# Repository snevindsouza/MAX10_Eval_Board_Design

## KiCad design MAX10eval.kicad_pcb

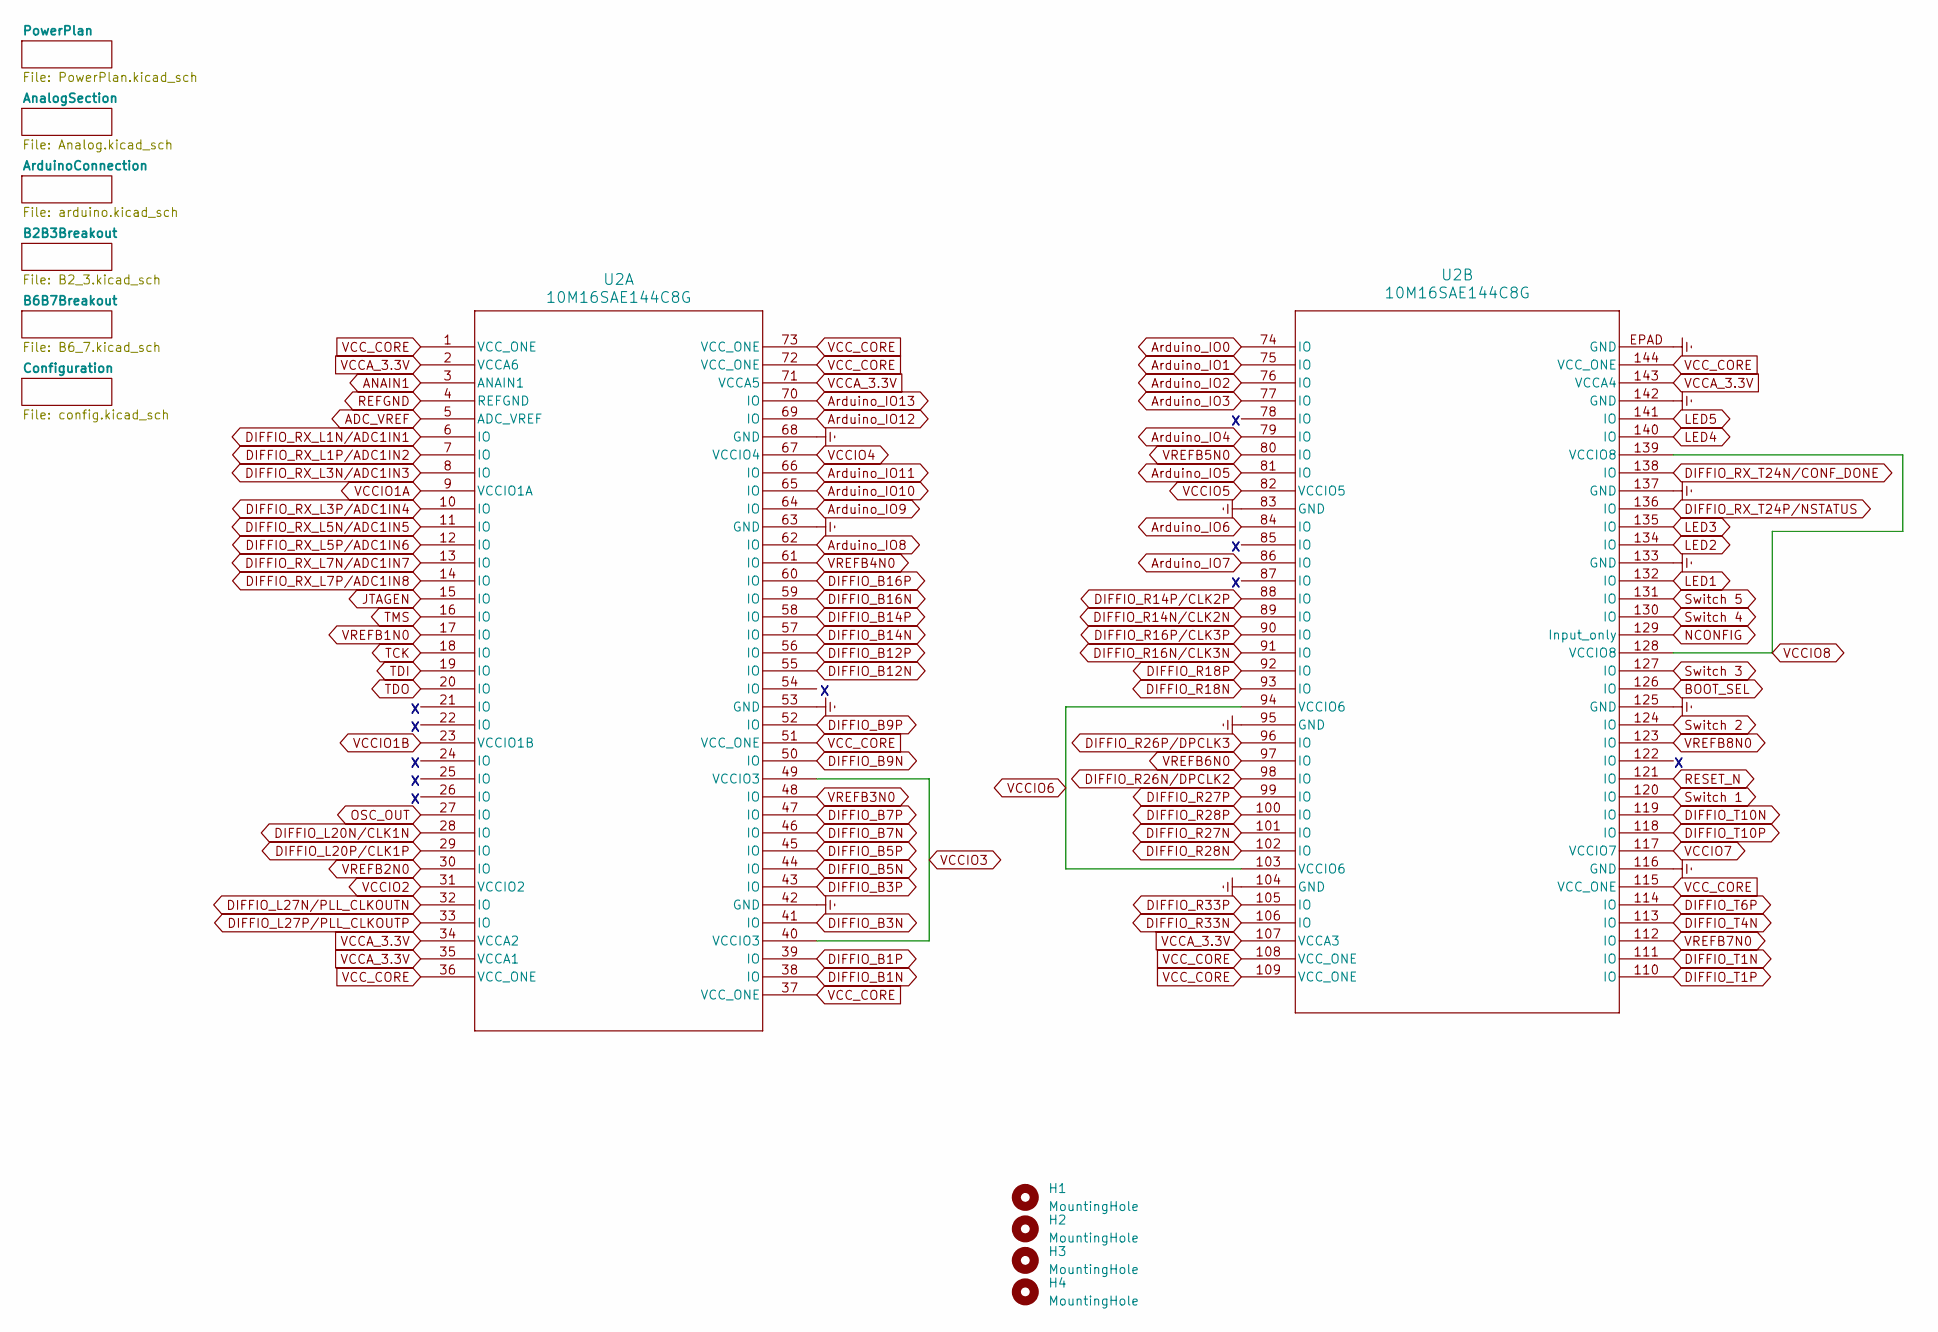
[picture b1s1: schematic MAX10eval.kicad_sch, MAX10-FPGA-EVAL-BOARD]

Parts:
H1, H2, H3, H4: MountingHole; MountingHole_3.2mm_M3
U2: 10M16SAE144C8G; 10M16SAE114C8G

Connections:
ADC_VREF: U2.5 (ADC_VREF); also elsewhere on the board
ANAIN1: U2.3 (ANAIN1); also elsewhere on the board
Arduino_IO0: U2.74 (IO); also elsewhere on the board
Arduino_IO1: U2.75 (IO); also elsewhere on the board
Arduino_IO2: U2.76 (IO); also elsewhere on the board
Arduino_IO3: U2.77 (IO); also elsewhere on the board
Arduino_IO4: U2.79 (IO); also elsewhere on the board
Arduino_IO5: U2.81 (IO); also elsewhere on the board
Arduino_IO6: U2.84 (IO); also elsewhere on the board
Arduino_IO7: U2.86 (IO); also elsewhere on the board
Arduino_IO8: U2.62 (IO); also elsewhere on the board
Arduino_IO9: U2.64 (IO); also elsewhere on the board
Arduino_IO10: U2.65 (IO); also elsewhere on the board
Arduino_IO11: U2.66 (IO); also elsewhere on the board
Arduino_IO12: U2.69 (IO); also elsewhere on the board
Arduino_IO13: U2.70 (IO); also elsewhere on the board
BOOT_SEL: U2.126 (IO); also elsewhere on the board
DIFFIO_B1N: U2.38 (IO); also elsewhere on the board
DIFFIO_B1P: U2.39 (IO); also elsewhere on the board
DIFFIO_B3N: U2.41 (IO); also elsewhere on the board
DIFFIO_B3P: U2.43 (IO); also elsewhere on the board
DIFFIO_B5N: U2.44 (IO); also elsewhere on the board
DIFFIO_B5P: U2.45 (IO); also elsewhere on the board
DIFFIO_B7N: U2.46 (IO); also elsewhere on the board
DIFFIO_B7P: U2.47 (IO); also elsewhere on the board
DIFFIO_B9N: U2.50 (IO); also elsewhere on the board
DIFFIO_B9P: U2.52 (IO); also elsewhere on the board
DIFFIO_B12N: U2.55 (IO); also elsewhere on the board
DIFFIO_B12P: U2.56 (IO); also elsewhere on the board
DIFFIO_B14N: U2.57 (IO); also elsewhere on the board
DIFFIO_B14P: U2.58 (IO); also elsewhere on the board
DIFFIO_B16N: U2.59 (IO); also elsewhere on the board
DIFFIO_B16P: U2.60 (IO); also elsewhere on the board
DIFFIO_L20N/CLK1N: U2.28 (IO); also elsewhere on the board
DIFFIO_L20P/CLK1P: U2.29 (IO); also elsewhere on the board
DIFFIO_L27N/PLL_CLKOUTN: U2.32 (IO); also elsewhere on the board
DIFFIO_L27P/PLL_CLKOUTP: U2.33 (IO); also elsewhere on the board
DIFFIO_R14N/CLK2N: U2.89 (IO); also elsewhere on the board
DIFFIO_R14P/CLK2P: U2.88 (IO); also elsewhere on the board
DIFFIO_R16N/CLK3N: U2.91 (IO); also elsewhere on the board
DIFFIO_R16P/CLK3P: U2.90 (IO); also elsewhere on the board
DIFFIO_R18N: U2.93 (IO); also elsewhere on the board
DIFFIO_R18P: U2.92 (IO); also elsewhere on the board
DIFFIO_R26N/DPCLK2: U2.98 (IO); also elsewhere on the board
DIFFIO_R26P/DPCLK3: U2.96 (IO); also elsewhere on the board
DIFFIO_R27N: U2.101 (IO); also elsewhere on the board
DIFFIO_R27P: U2.99 (IO); also elsewhere on the board
DIFFIO_R28N: U2.102 (IO); also elsewhere on the board
DIFFIO_R28P: U2.100 (IO); also elsewhere on the board
DIFFIO_R33N: U2.106 (IO); also elsewhere on the board
DIFFIO_R33P: U2.105 (IO); also elsewhere on the board
DIFFIO_RX_L1N/ADC1IN1: U2.6 (IO); also elsewhere on the board
DIFFIO_RX_L1P/ADC1IN2: U2.7 (IO); also elsewhere on the board
DIFFIO_RX_L3N/ADC1IN3: U2.8 (IO); also elsewhere on the board
DIFFIO_RX_L3P/ADC1IN4: U2.10 (IO); also elsewhere on the board
DIFFIO_RX_L5N/ADC1IN5: U2.11 (IO); also elsewhere on the board
DIFFIO_RX_L5P/ADC1IN6: U2.12 (IO); also elsewhere on the board
DIFFIO_RX_L7N/ADC1IN7: U2.13 (IO); also elsewhere on the board
DIFFIO_RX_L7P/ADC1IN8: U2.14 (IO); also elsewhere on the board
DIFFIO_RX_T24N/CONF_DONE: U2.138 (IO); also elsewhere on the board
DIFFIO_RX_T24P/NSTATUS: U2.136 (IO); also elsewhere on the board
DIFFIO_T1N: U2.111 (IO); also elsewhere on the board
DIFFIO_T1P: U2.110 (IO); also elsewhere on the board
DIFFIO_T4N: U2.113 (IO); also elsewhere on the board
DIFFIO_T6P: U2.114 (IO); also elsewhere on the board
DIFFIO_T10N: U2.119 (IO); also elsewhere on the board
DIFFIO_T10P: U2.118 (IO); also elsewhere on the board
Earth: U2.42 (GND), U2.53 (GND), U2.63 (GND), U2.68 (GND), U2.83 (GND), U2.95 (GND), U2.104 (GND), U2.116 (GND), U2.125 (GND), U2.133 (GND), U2.137 (GND), U2.142 (GND), U2.EPAD (GND); also elsewhere on the board
JTAGEN: U2.15 (IO); also elsewhere on the board
LED1: U2.132 (IO); also elsewhere on the board
LED2: U2.134 (IO); also elsewhere on the board
LED3: U2.135 (IO); also elsewhere on the board
LED4: U2.140 (IO); also elsewhere on the board
LED5: U2.141 (IO); also elsewhere on the board
NCONFIG: U2.129 (Input_only); also elsewhere on the board
OSC_OUT: U2.27 (IO); also elsewhere on the board
REFGND: U2.4 (REFGND); also elsewhere on the board
RESET_N: U2.121 (IO); also elsewhere on the board
Switch 1: U2.120 (IO); also elsewhere on the board
Switch 2: U2.124 (IO); also elsewhere on the board
Switch 3: U2.127 (IO); also elsewhere on the board
Switch 4: U2.130 (IO); also elsewhere on the board
Switch 5: U2.131 (IO); also elsewhere on the board
TCK: U2.18 (IO); also elsewhere on the board
TDI: U2.19 (IO); also elsewhere on the board
TDO: U2.20 (IO); also elsewhere on the board
TMS: U2.16 (IO); also elsewhere on the board
VCCA_3.3V: U2.2 (VCCA6), U2.34 (VCCA2), U2.35 (VCCA1), U2.71 (VCCA5), U2.107 (VCCA3), U2.143 (VCCA4); also elsewhere on the board
VCCIO1A: U2.9 (VCCIO1A); also elsewhere on the board
VCCIO1B: U2.23 (VCCIO1B); also elsewhere on the board
VCCIO2: U2.31 (VCCIO2); also elsewhere on the board
VCCIO3: U2.40 (VCCIO3), U2.49 (VCCIO3); also elsewhere on the board
VCCIO4: U2.67 (VCCIO4); also elsewhere on the board
VCCIO5: U2.82 (VCCIO5); also elsewhere on the board
VCCIO6: U2.94 (VCCIO6), U2.103 (VCCIO6); also elsewhere on the board
VCCIO7: U2.117 (VCCIO7); also elsewhere on the board
VCCIO8: U2.128 (VCCIO8), U2.139 (VCCIO8); also elsewhere on the board
VCC_CORE: U2.1 (VCC_ONE), U2.36 (VCC_ONE), U2.37 (VCC_ONE), U2.51 (VCC_ONE), U2.72 (VCC_ONE), U2.73 (VCC_ONE), U2.108 (VCC_ONE), U2.109 (VCC_ONE), U2.115 (VCC_ONE), U2.144 (VCC_ONE); also elsewhere on the board
VREFB1N0: U2.17 (IO); also elsewhere on the board
VREFB2N0: U2.30 (IO); also elsewhere on the board
VREFB3N0: U2.48 (IO); also elsewhere on the board
VREFB4N0: U2.61 (IO); also elsewhere on the board
VREFB5N0: U2.80 (IO); also elsewhere on the board
VREFB6N0: U2.97 (IO); also elsewhere on the board
VREFB7N0: U2.112 (IO); also elsewhere on the board
VREFB8N0: U2.123 (IO); also elsewhere on the board

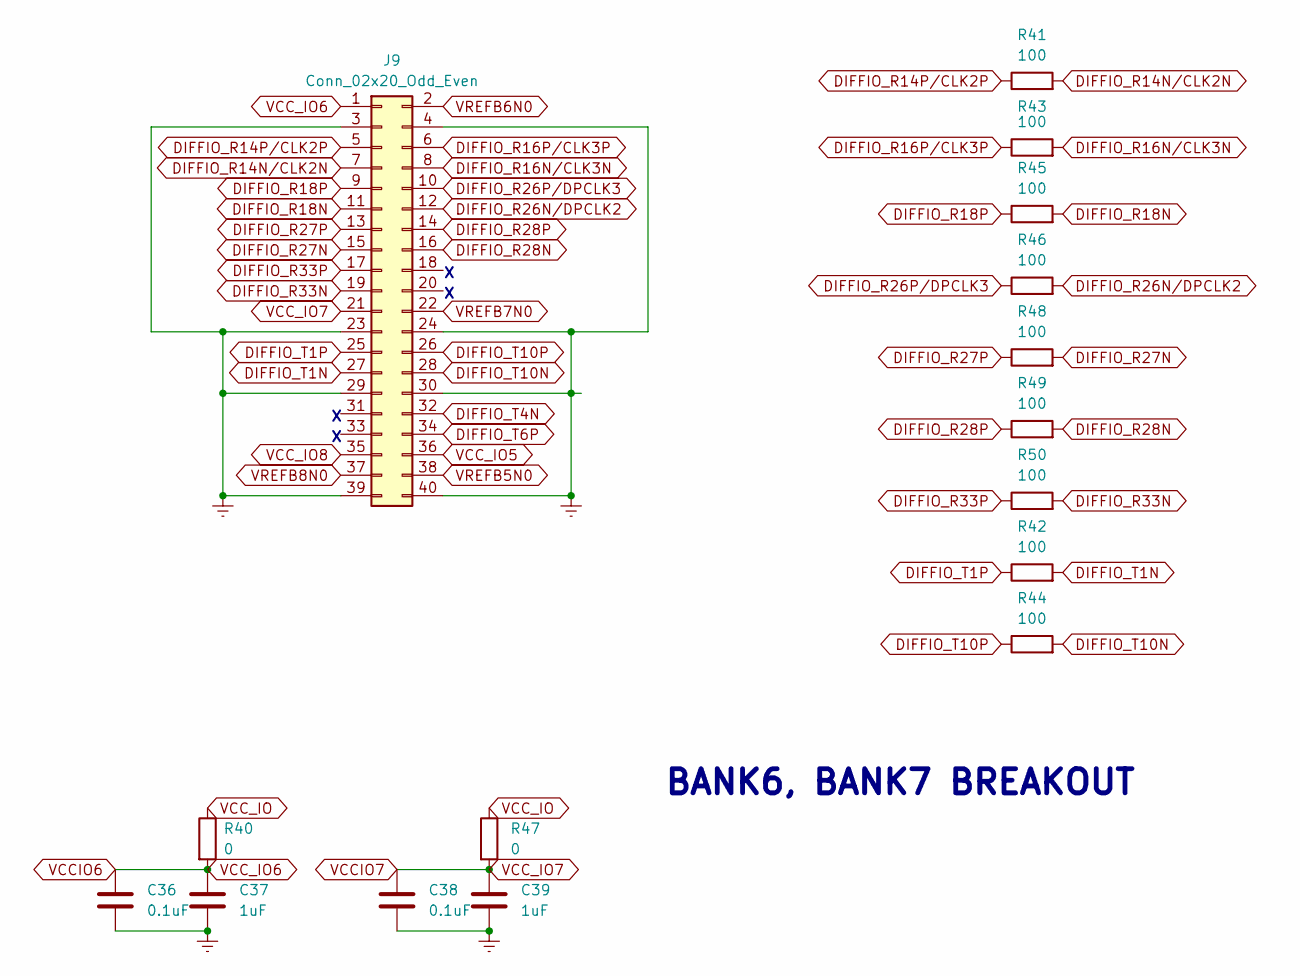
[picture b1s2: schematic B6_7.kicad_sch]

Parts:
C36, C38: 0.1uF; C_0201_0603Metric
C37, C39: 1uF; C_0201_0603Metric
J9: Conn_02x20_Odd_Even; PinHeader_2x20_P2.54mm_Vertical
R40, R47: 0; R_0201_0603Metric
R41, R42, R43, R44, R45, R46, R48, R49, R50: 100; R_0201_0603Metric

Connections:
DIFFIO_R14N/CLK2N: J9.7, R41.2; also elsewhere on the board
DIFFIO_R14P/CLK2P: J9.5, R41.1; also elsewhere on the board
DIFFIO_R16N/CLK3N: J9.8, R43.2; also elsewhere on the board
DIFFIO_R16P/CLK3P: J9.6, R43.1; also elsewhere on the board
DIFFIO_R18N: J9.11, R45.2; also elsewhere on the board
DIFFIO_R18P: J9.9, R45.1; also elsewhere on the board
DIFFIO_R26N/DPCLK2: J9.12, R46.2; also elsewhere on the board
DIFFIO_R26P/DPCLK3: J9.10, R46.1; also elsewhere on the board
DIFFIO_R27N: J9.15, R48.2; also elsewhere on the board
DIFFIO_R27P: J9.13, R48.1; also elsewhere on the board
DIFFIO_R28N: J9.16, R49.2; also elsewhere on the board
DIFFIO_R28P: J9.14, R49.1; also elsewhere on the board
DIFFIO_R33N: J9.19, R50.2; also elsewhere on the board
DIFFIO_R33P: J9.17, R50.1; also elsewhere on the board
DIFFIO_T1N: J9.27, R42.2; also elsewhere on the board
DIFFIO_T1P: J9.25, R42.1; also elsewhere on the board
DIFFIO_T4N: J9.32; also elsewhere on the board
DIFFIO_T6P: J9.34; also elsewhere on the board
DIFFIO_T10N: J9.28, R44.2; also elsewhere on the board
DIFFIO_T10P: J9.26, R44.1; also elsewhere on the board
Earth: C36.2, C37.2, C38.2, C39.2, J9.3, J9.4, J9.23, J9.24, J9.29, J9.30, J9.39, J9.40; also elsewhere on the board
VCCIO5: J9.36; also elsewhere on the board
VCCIO6: C36.1, C37.1, J9.1, R40.2; also elsewhere on the board
VCCIO7: C38.1, C39.1, J9.21, R47.2; also elsewhere on the board
VCCIO8: J9.35; also elsewhere on the board
VCC_IO: R40.1, R47.1; also elsewhere on the board
VREFB5N0: J9.38; also elsewhere on the board
VREFB6N0: J9.2; also elsewhere on the board
VREFB7N0: J9.22; also elsewhere on the board
VREFB8N0: J9.37; also elsewhere on the board

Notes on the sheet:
BANK6, BANK7 BREAKOUT

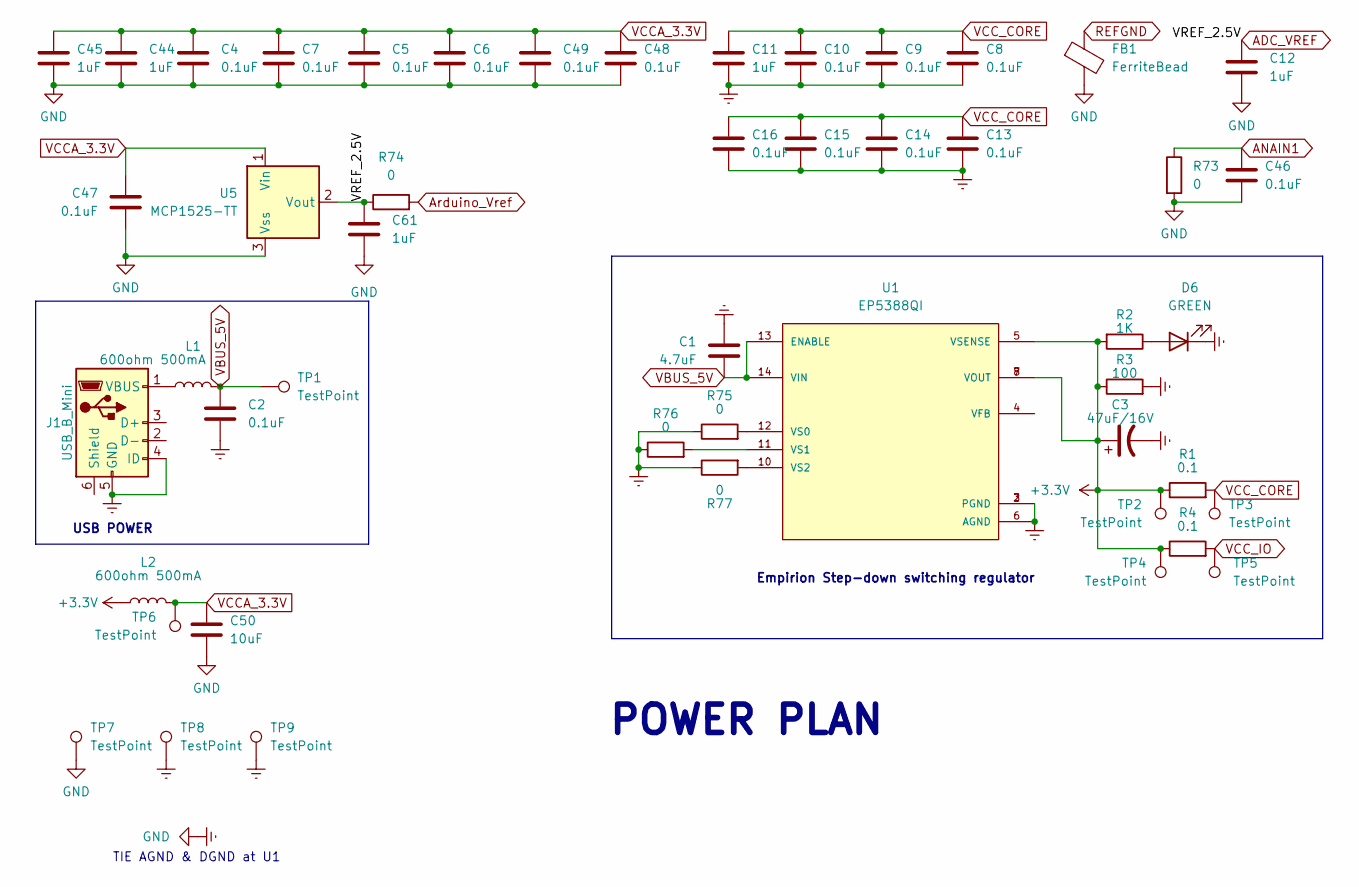
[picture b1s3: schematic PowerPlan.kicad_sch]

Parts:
C1: 4.7uF; C_0201_0603Metric
C2, C4, C5, C6, C7, C8, C9, C10, C13, C14, C15, C16, C46, C47, C48, C49: 0.1uF; C_0201_0603Metric
C3: 47uF/16V; C_Elec_3x5.4
C11, C12, C44, C45, C61: 1uF; C_0201_0603Metric
C50: 10uF; C_0201_0603Metric
D6: GREEN; LED_0201_0603Metric
FB1: FerriteBead; L_0201_0603Metric
J1: USB_B_Mini; USB_Mini-B_Lumberg_2486_01_Horizontal
L1, L2: 600ohm 500mA; L_0201_0603Metric
R1, R4: 0.1; RESC2012X60N
R2: 1K; R_0201_0603Metric
R3: 100; RESC2012X60N
R73, R74, R75, R76, R77: 0; R_0201_0603Metric
TP1, TP2, TP3, TP4, TP5, TP6, TP7, TP8, TP9: TestPoint; TestPoint_THTPad_1.0x1.0mm_Drill0.5mm
U1: EP5388QI; CONV_EP5388QI; PARTREV H
U5: MCP1525-TT; SOT-23

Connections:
+3.3V: C3.1, L2.1, R1.1, R2.2, R3.1, R4.1, TP2.1, TP4.1, U1.5 (VSENSE), U1.7 (VOUT), U1.8 (VOUT); also elsewhere on the board
ADC_VREF: C12.1, C61.1, R74.1, U5.2 (Vout); also elsewhere on the board
ANAIN1: C46.1, R73.1; also elsewhere on the board
Arduino_Vref: R74.2; also elsewhere on the board
Earth: C1.2, C2.2, C3.2, C4.2, C5.2, C6.2, C7.2, C8.2, C9.2, C10.2, C11.2, C12.2, C13.2, C14.2, C15.2, C16.2, C44.2, C45.2, C46.2, C47.2, C48.2, C49.2, C50.2, C61.2, D6.1 (K), FB1.2, J1.4 (ID), J1.5 (GND), R3.2, R73.2, R75.1, R76.1, R77.1, TP7.1, TP8.1, TP9.1, U1.2 (PGND), U1.3 (PGND), U1.6 (AGND), U5.3 (Vss); also elsewhere on the board
unnamed: D6.2 (A), R2.1
unnamed: J1.1 (VBUS), L1.1
unnamed: R75.2, U1.12 (VS0)
unnamed: R76.2, U1.11 (VS1)
unnamed: R77.2, U1.10 (VS2)
REFGND: FB1.1; also elsewhere on the board
VBUS_5V: C1.1, C2.1, L1.2, TP1.1, U1.13 (ENABLE), U1.14 (VIN); also elsewhere on the board
VCCA_3.3V: C4.1, C5.1, C6.1, C7.1, C44.1, C45.1, C47.1, C48.1, C49.1, C50.1, L2.2, TP6.1, U5.1 (Vin); also elsewhere on the board
VCC_CORE: C8.1, C9.1, C10.1, C11.1, C13.1, C14.1, C15.1, C16.1, R1.2, TP3.1; also elsewhere on the board
VCC_IO: R4.2, TP5.1; also elsewhere on the board

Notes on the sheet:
TIE AGND & DGND at U1
Empirion Step-down switching regulator
POWER PLAN
USB POWER

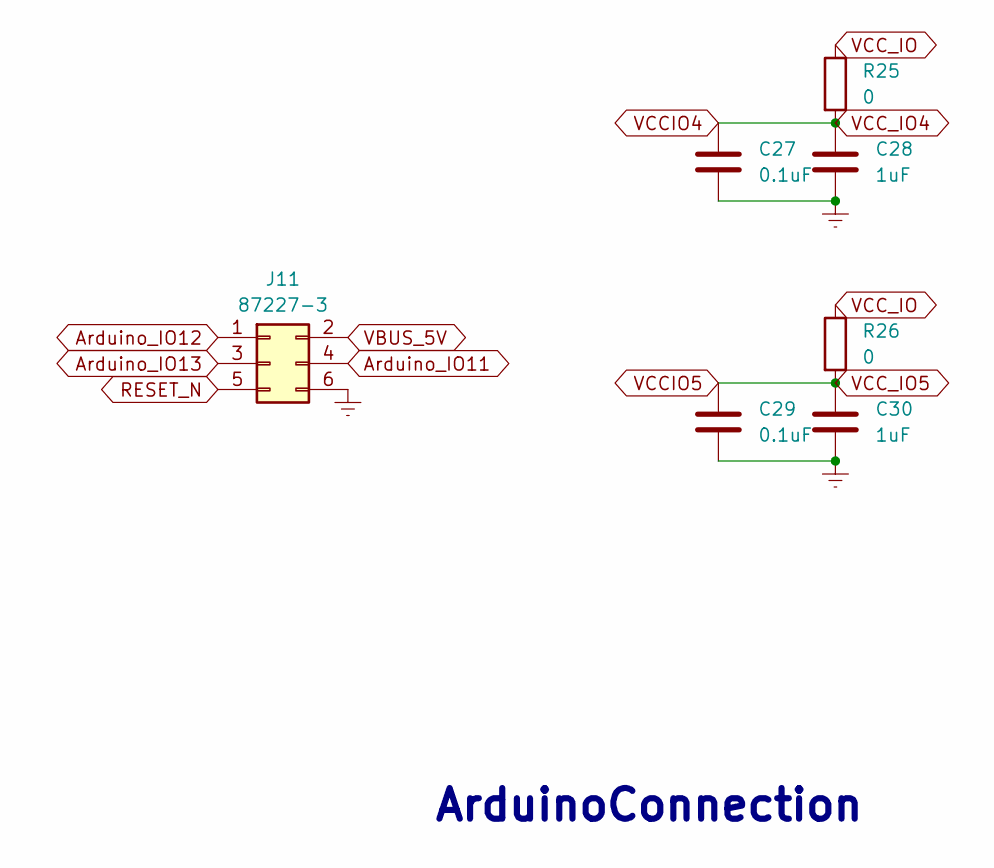
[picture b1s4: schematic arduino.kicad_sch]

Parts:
C27, C29: 0.1uF; C_0201_0603Metric
C28, C30: 1uF; C_0201_0603Metric
J11: 87227-3; PinHeader_2x03_P2.54mm_Vertical
R25, R26: 0; R_0201_0603Metric

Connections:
Arduino_IO11: J11.4; also elsewhere on the board
Arduino_IO12: J11.1; also elsewhere on the board
Arduino_IO13: J11.3; also elsewhere on the board
Earth: C27.2, C28.2, C29.2, C30.2, J11.6; also elsewhere on the board
RESET_N: J11.5; also elsewhere on the board
VBUS_5V: J11.2; also elsewhere on the board
VCCIO4: C27.1, C28.1, R25.2; also elsewhere on the board
VCCIO5: C29.1, C30.1, R26.2; also elsewhere on the board
VCC_IO: R25.1, R26.1; also elsewhere on the board

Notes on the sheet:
ArduinoConnection

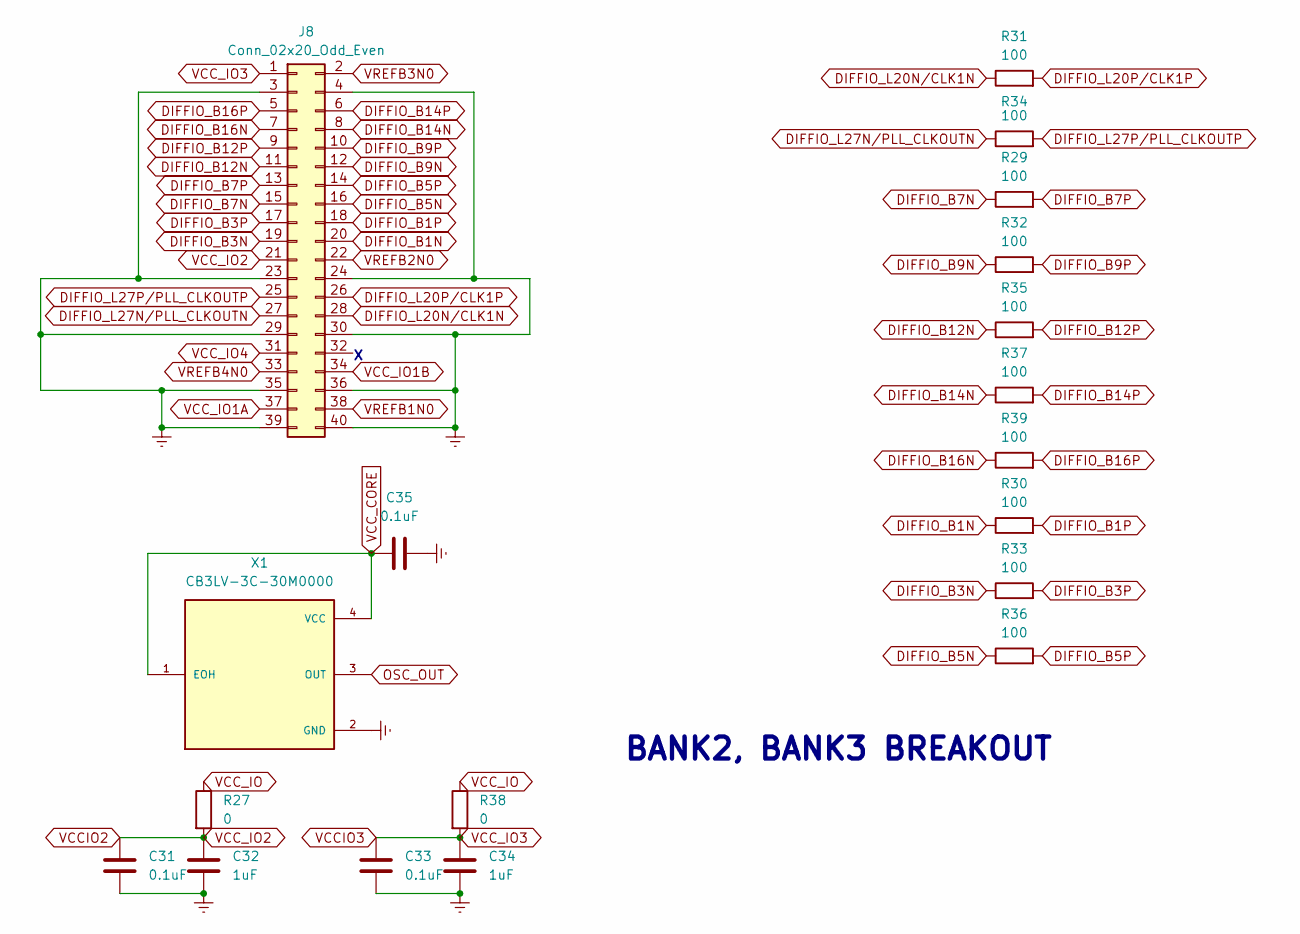
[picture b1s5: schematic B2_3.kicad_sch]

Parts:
C31, C33, C35: 0.1uF; C_0201_0603Metric
C32, C34: 1uF; C_0201_0603Metric
J8: Conn_02x20_Odd_Even; PinHeader_2x20_P2.54mm_Vertical
R27, R38: 0; R_0201_0603Metric
R29, R30, R31, R32, R33, R34, R35, R36, R37, R39: 100; R_0201_0603Metric
X1: CB3LV-3C-30M0000; OSCCC700X500X180-4N

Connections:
DIFFIO_B1N: J8.20, R30.1; also elsewhere on the board
DIFFIO_B1P: J8.18, R30.2; also elsewhere on the board
DIFFIO_B3N: J8.19, R33.1; also elsewhere on the board
DIFFIO_B3P: J8.17, R33.2; also elsewhere on the board
DIFFIO_B5N: J8.16, R36.1; also elsewhere on the board
DIFFIO_B5P: J8.14, R36.2; also elsewhere on the board
DIFFIO_B7N: J8.15, R29.1; also elsewhere on the board
DIFFIO_B7P: J8.13, R29.2; also elsewhere on the board
DIFFIO_B9N: J8.12, R32.1; also elsewhere on the board
DIFFIO_B9P: J8.10, R32.2; also elsewhere on the board
DIFFIO_B12N: J8.11, R35.1; also elsewhere on the board
DIFFIO_B12P: J8.9, R35.2; also elsewhere on the board
DIFFIO_B14N: J8.8, R37.1; also elsewhere on the board
DIFFIO_B14P: J8.6, R37.2; also elsewhere on the board
DIFFIO_B16N: J8.7, R39.1; also elsewhere on the board
DIFFIO_B16P: J8.5, R39.2; also elsewhere on the board
DIFFIO_L20N/CLK1N: J8.28, R31.1; also elsewhere on the board
DIFFIO_L20P/CLK1P: J8.26, R31.2; also elsewhere on the board
DIFFIO_L27N/PLL_CLKOUTN: J8.27, R34.1; also elsewhere on the board
DIFFIO_L27P/PLL_CLKOUTP: J8.25, R34.2; also elsewhere on the board
Earth: C31.2, C32.2, C33.2, C34.2, C35.2, J8.3, J8.4, J8.23, J8.24, J8.29, J8.30, J8.35, J8.36, J8.39, J8.40, X1.2 (GND); also elsewhere on the board
OSC_OUT: X1.3 (OUT); also elsewhere on the board
VCCIO1A: J8.37; also elsewhere on the board
VCCIO1B: J8.34; also elsewhere on the board
VCCIO2: C31.1, C32.1, J8.21, R27.2; also elsewhere on the board
VCCIO3: C33.1, C34.1, J8.1, R38.2; also elsewhere on the board
VCCIO4: J8.31; also elsewhere on the board
VCC_CORE: C35.1, X1.1 (EOH), X1.4 (VCC); also elsewhere on the board
VCC_IO: R27.1, R38.1; also elsewhere on the board
VREFB1N0: J8.38; also elsewhere on the board
VREFB2N0: J8.22; also elsewhere on the board
VREFB3N0: J8.2; also elsewhere on the board
VREFB4N0: J8.33; also elsewhere on the board

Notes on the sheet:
BANK2, BANK3 BREAKOUT

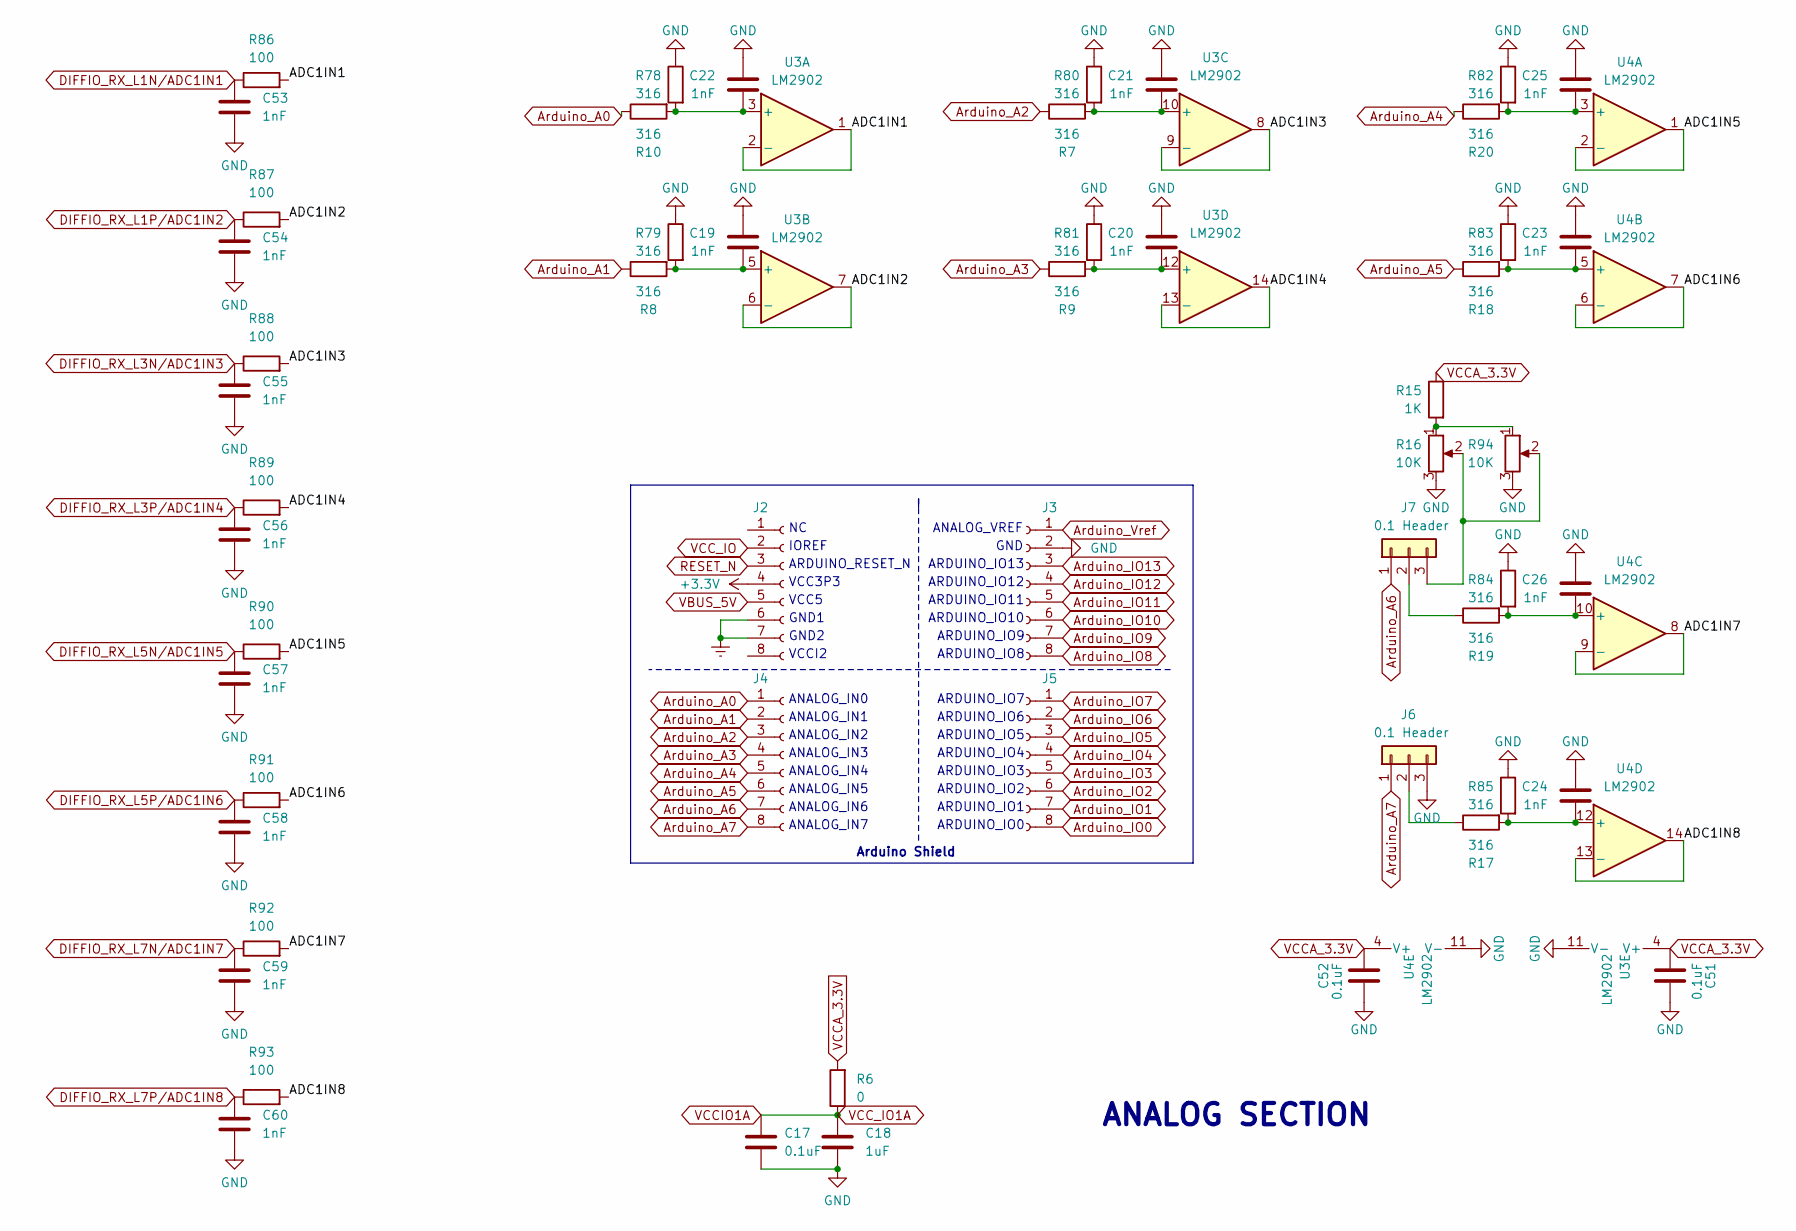
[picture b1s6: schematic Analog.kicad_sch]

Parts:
C17, C51, C52: 0.1uF; C_0201_0603Metric
C18: 1uF; C_0201_0603Metric
C19, C20, C21, C22, C23, C24, C25, C26, C53, C54, C55, C56, C57, C58, C59, C60: 1nF; C_0201_0603Metric
J2, J3, J4, J5: Conn_01x08_Socket; PinSocket_1x08_P2.54mm_Vertical
J6, J7: 0.1 Header; PinHeader_1x03_P2.54mm_Vertical
R6: 0; R_0201_0603Metric
R7, R8, R9, R10, R17, R18, R19, R20, R78, R79, R80, R81, R82, R83, R84, R85: 316; R_0201_0603Metric
R15: 1K; R_0201_0603Metric
R16: 10K; Potentiometer_Vishay_TS53YJ_Vertical
R86, R87, R88, R89, R90, R91, R92, R93: 100; R_0201_0603Metric
R94: 10K; Potentiometer_ACP_CA9-H5_Horizontal
U3, U4: LM2902; SOIC127P600X175-14N

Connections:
+3.3V: J2.4; also elsewhere on the board
/AnalogSection/ADC1IN1: R86.2, U3.1, U3.2 (-)
/AnalogSection/ADC1IN2: R87.2, U3.6 (-), U3.7
/AnalogSection/ADC1IN3: R88.2, U3.8, U3.9 (-)
/AnalogSection/ADC1IN4: R89.2, U3.13 (-), U3.14
/AnalogSection/ADC1IN5: R90.2, U4.1, U4.2 (-)
/AnalogSection/ADC1IN6: R91.2, U4.6 (-), U4.7
/AnalogSection/ADC1IN7: R92.2, U4.8, U4.9 (-)
/AnalogSection/ADC1IN8: R93.2, U4.13 (-), U4.14
Arduino_A0: J4.1, R10.1
Arduino_A1: J4.2, R8.1
Arduino_A2: J4.3, R7.1
Arduino_A3: J4.4, R9.1
Arduino_A4: J4.5, R20.1
Arduino_A5: J4.6, R18.1
Arduino_A6: J4.7, J7.1
Arduino_A7: J4.8, J6.1
Arduino_IO0: J5.8; also elsewhere on the board
Arduino_IO1: J5.7; also elsewhere on the board
Arduino_IO2: J5.6; also elsewhere on the board
Arduino_IO3: J5.5; also elsewhere on the board
Arduino_IO4: J5.4; also elsewhere on the board
Arduino_IO5: J5.3; also elsewhere on the board
Arduino_IO6: J5.2; also elsewhere on the board
Arduino_IO7: J5.1; also elsewhere on the board
Arduino_IO8: J3.8; also elsewhere on the board
Arduino_IO9: J3.7; also elsewhere on the board
Arduino_IO10: J3.6; also elsewhere on the board
Arduino_IO11: J3.5; also elsewhere on the board
Arduino_IO12: J3.4; also elsewhere on the board
Arduino_IO13: J3.3; also elsewhere on the board
Arduino_Vref: J3.1; also elsewhere on the board
DIFFIO_RX_L1N/ADC1IN1: C53.1, R86.1; also elsewhere on the board
DIFFIO_RX_L1P/ADC1IN2: C54.1, R87.1; also elsewhere on the board
DIFFIO_RX_L3N/ADC1IN3: C55.1, R88.1; also elsewhere on the board
DIFFIO_RX_L3P/ADC1IN4: C56.1, R89.1; also elsewhere on the board
DIFFIO_RX_L5N/ADC1IN5: C57.1, R90.1; also elsewhere on the board
DIFFIO_RX_L5P/ADC1IN6: C58.1, R91.1; also elsewhere on the board
DIFFIO_RX_L7N/ADC1IN7: C59.1, R92.1; also elsewhere on the board
DIFFIO_RX_L7P/ADC1IN8: C60.1, R93.1; also elsewhere on the board
Earth: C17.2, C18.2, C19.1, C20.1, C21.1, C22.1, C23.1, C24.1, C25.1, C26.1, C51.2, C52.2, C53.2, C54.2, C55.2, C56.2, C57.2, C58.2, C59.2, C60.2, J2.6, J2.7, J3.2, J6.3, R16.3, R78.1, R79.1, R80.1, R81.1, R82.1, R83.1, R84.1, R85.1, R94.3, U3.11 (V-), U4.11 (V-); also elsewhere on the board
unnamed: J6.2, R17.1
unnamed: J7.2, R19.1
unnamed: J7.3, R16.2, R94.2
unnamed: R15.2, R16.1, R94.1
unnamed: C22.2, R10.2, R78.2, U3.3 (+)
unnamed: C19.2, R8.2, R79.2, U3.5 (+)
unnamed: C21.2, R7.2, R80.2, U3.10 (+)
unnamed: C20.2, R9.2, R81.2, U3.12 (+)
unnamed: C25.2, R20.2, R82.2, U4.3 (+)
unnamed: C23.2, R18.2, R83.2, U4.5 (+)
unnamed: C26.2, R19.2, R84.2, U4.10 (+)
unnamed: C24.2, R17.2, R85.2, U4.12 (+)
RESET_N: J2.3; also elsewhere on the board
VBUS_5V: J2.5; also elsewhere on the board
VCCA_3.3V: C51.1, C52.1, R6.2, R15.1, U3.4 (V+), U4.4 (V+); also elsewhere on the board
VCCIO1A: C17.1, C18.1, R6.1; also elsewhere on the board
VCC_IO: J2.2; also elsewhere on the board

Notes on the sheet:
ARDUINO_IO13
ARDUINO_IO4
ANALOG_IN2
ARDUINO_IO12
ARDUINO_RESET_N
ANALOG SECTION
GND
ARDUINO_IO2
ARDUINO_IO10
ANALOG_IN0
IOREF
VCCI2
ARDUINO_IO9
ANALOG_IN1
ARDUINO_IO0
ANALOG_IN5
ARDUINO_IO8
ARDUINO_IO7
ANALOG_IN6
GND1
ANALOG_IN7
ARDUINO_IO1
ANALOG_IN4
ANALOG_IN3
Arduino Shield
ANALOG_VREF
VCC3P3
ARDUINO_IO11
VCC5
ARDUINO_IO6
ARDUINO_IO5
GND2
ARDUINO_IO3

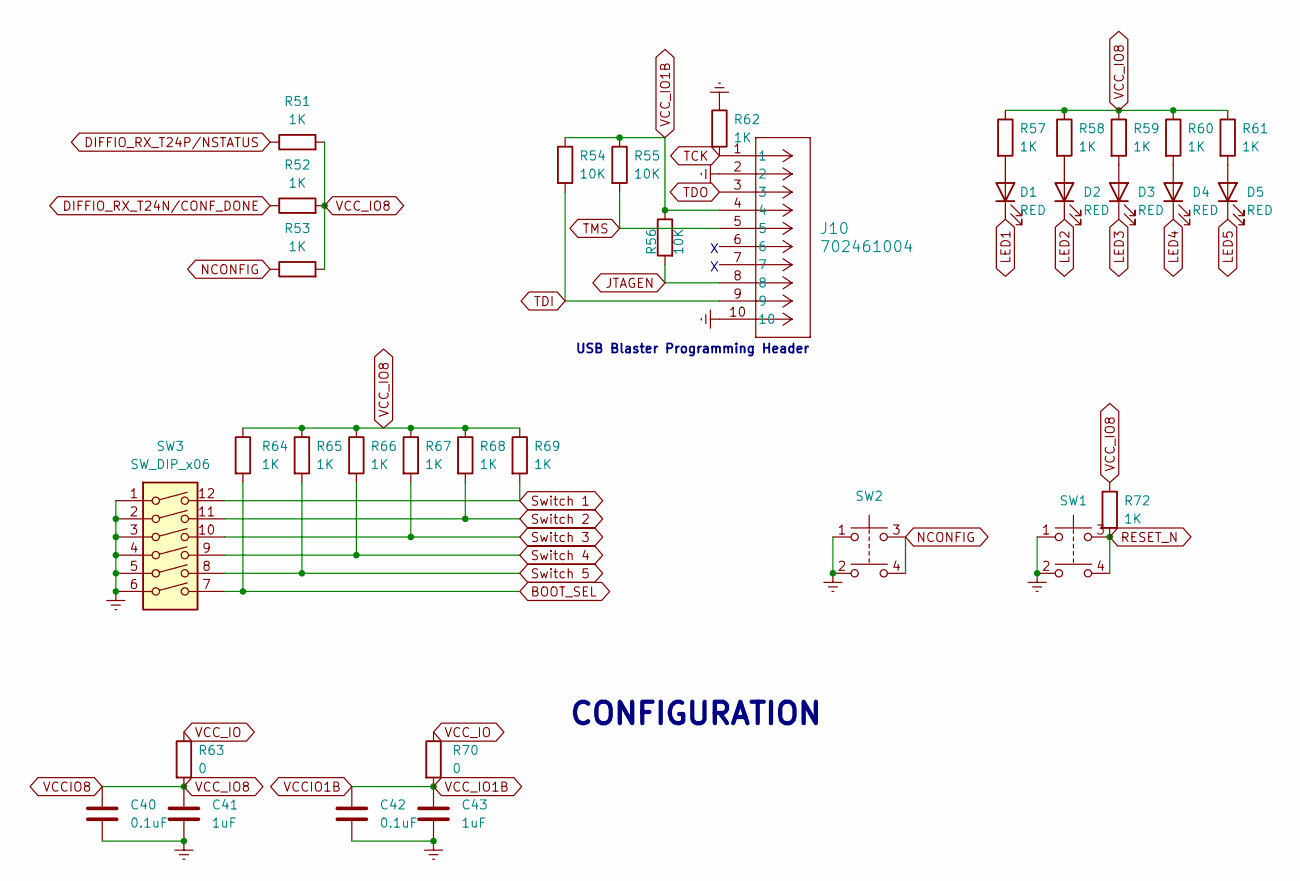
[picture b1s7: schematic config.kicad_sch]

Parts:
C40, C42: 0.1uF; C_0201_0603Metric
C41, C43: 1uF; C_0201_0603Metric
D1, D2, D3, D4, D5: RED; LED_0201_0603Metric
J10: 702461004; CON_702461004_MOL
R51, R52, R53, R57, R58, R59, R60, R61, R62, R64, R65, R66, R67, R68, R69, R72: 1K; R_0201_0603Metric
R54, R55, R56: 10K; R_0201_0603Metric
R63, R70: 0; R_0201_0603Metric
SW1, SW2: SWITCH_43SMTR92LFS
SW3: SW_DIP_x06; SW_DIP_SPSTx06_Slide_6.7x16.8mm_W6.73mm_P2.54mm_LowProfile_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

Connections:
BOOT_SEL: R64.2, SW3.7; also elsewhere on the board
DIFFIO_RX_T24N/CONF_DONE: R52.1; also elsewhere on the board
DIFFIO_RX_T24P/NSTATUS: R51.1; also elsewhere on the board
Earth: C40.2, C41.2, C42.2, C43.2, J10.2, J10.10, R62.1, SW1.1, SW1.2, SW2.1, SW2.2, SW3.1, SW3.2, SW3.3, SW3.4, SW3.5, SW3.6; also elsewhere on the board
JTAGEN: J10.8, R56.2; also elsewhere on the board
LED1: D1.1 (K); also elsewhere on the board
LED2: D2.1 (K); also elsewhere on the board
LED3: D3.1 (K); also elsewhere on the board
LED4: D4.1 (K); also elsewhere on the board
LED5: D5.1 (K); also elsewhere on the board
NCONFIG: R53.1, SW2.3, SW2.4; also elsewhere on the board
unnamed: D1.2 (A), R57.2
unnamed: D2.2 (A), R58.2
unnamed: D3.2 (A), R59.2
unnamed: D4.2 (A), R60.2
unnamed: D5.2 (A), R61.2
RESET_N: R72.2, SW1.3, SW1.4; also elsewhere on the board
Switch 1: R69.2, SW3.12; also elsewhere on the board
Switch 2: R68.2, SW3.11; also elsewhere on the board
Switch 3: R67.2, SW3.10; also elsewhere on the board
Switch 4: R66.2, SW3.9; also elsewhere on the board
Switch 5: R65.2, SW3.8; also elsewhere on the board
TCK: J10.1, R62.2; also elsewhere on the board
TDI: J10.9, R54.2; also elsewhere on the board
TDO: J10.3; also elsewhere on the board
TMS: J10.5, R55.2; also elsewhere on the board
VCCIO1B: C42.1, C43.1, J10.4, R54.1, R55.1, R56.1, R70.2; also elsewhere on the board
VCCIO8: C40.1, C41.1, R51.2, R52.2, R53.2, R57.1, R58.1, R59.1, R60.1, R61.1, R63.2, R64.1, R65.1, R66.1, R67.1, R68.1, R69.1, R72.1; also elsewhere on the board
VCC_IO: R63.1, R70.1; also elsewhere on the board

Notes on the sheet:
USB Blaster Programming Header
CONFIGURATION
